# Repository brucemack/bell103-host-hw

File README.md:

Overview
========

Complete Bell 103 subscriber line interface simulator.

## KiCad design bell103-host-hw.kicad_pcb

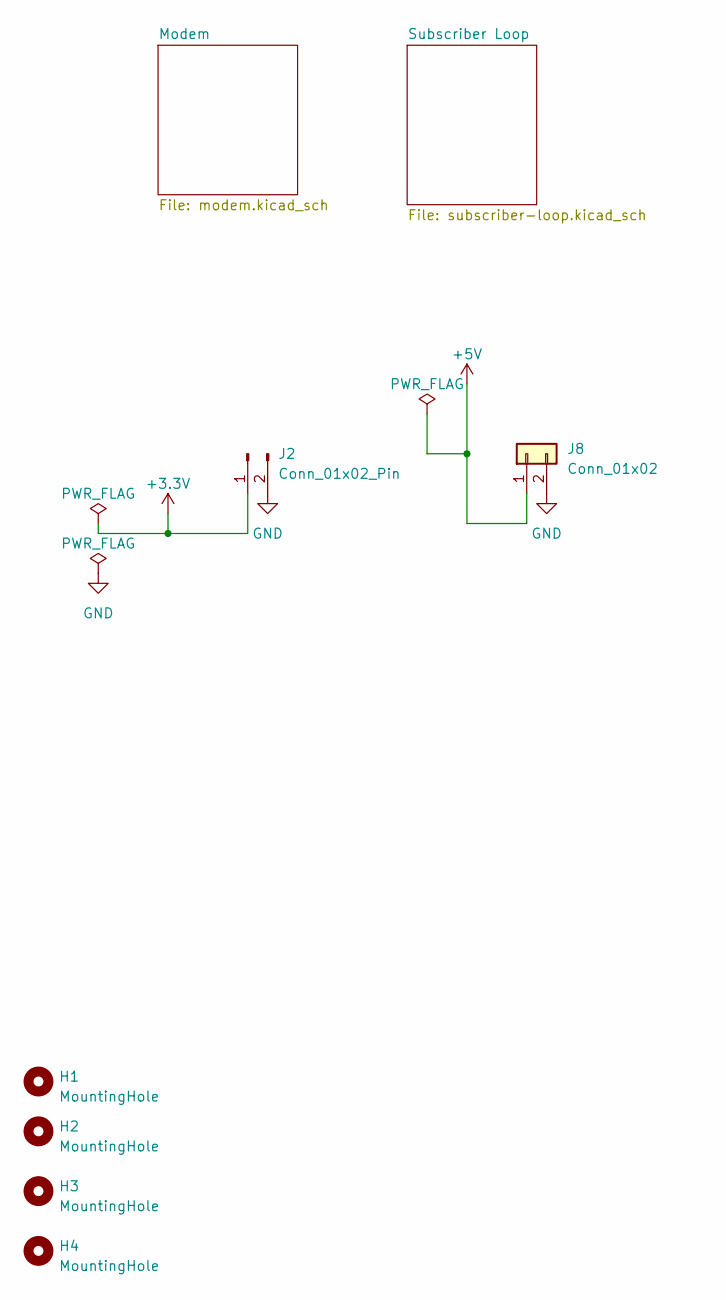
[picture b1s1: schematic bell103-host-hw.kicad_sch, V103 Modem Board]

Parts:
H1, H2, H3, H4: MountingHole; MountingHole_4mm
J2: Conn_01x02_Pin; PinHeader_1x02_P2.54mm_Vertical
J8: Conn_01x02; PinHeader_1x02_P2.54mm_Vertical

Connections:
+3.3V: J2.1; also elsewhere on the board
+5V: J8.1; also elsewhere on the board
GND: J2.2, J8.2; also elsewhere on the board

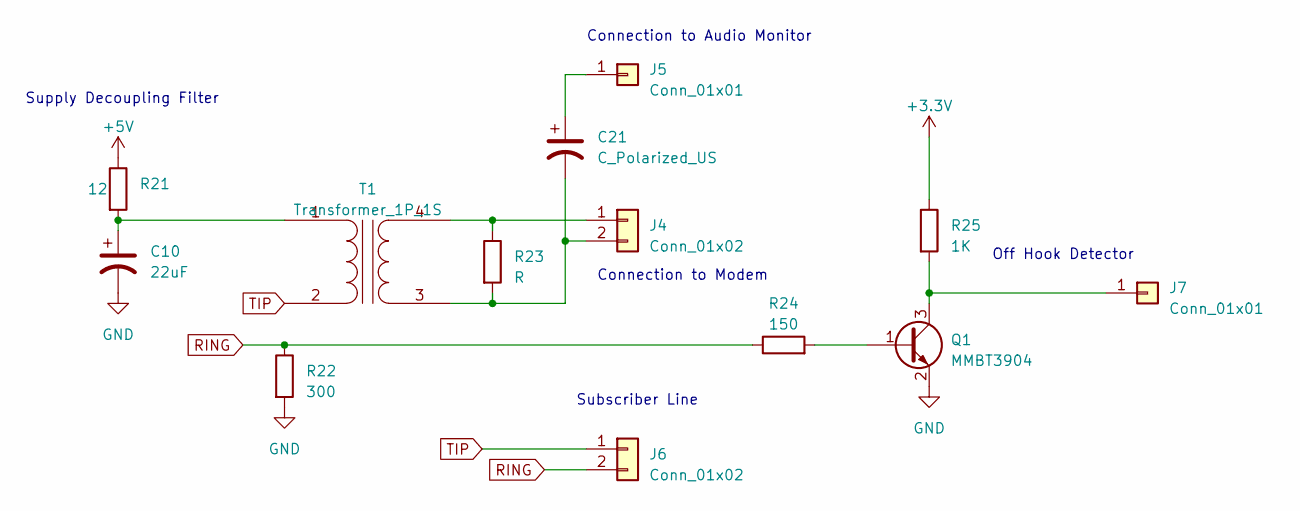
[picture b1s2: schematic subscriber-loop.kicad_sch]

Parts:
C10: 22uF; CP_Radial_D5.0mm_P2.50mm
C21: C_Polarized_US; CP_Radial_D5.0mm_P2.50mm
J4, J6: Conn_01x02; PinHeader_1x02_P2.54mm_Vertical
J5, J7: Conn_01x01; PinHeader_1x01_P2.54mm_Vertical
Q1: MMBT3904; SOT-23
R21: 12; R_0805_2012Metric_Pad1.20x1.40mm_HandSolder
R22: 300; R_0805_2012Metric_Pad1.20x1.40mm_HandSolder
R23: R; R_0805_2012Metric_Pad1.20x1.40mm_HandSolder
R24: 150; R_0805_2012Metric_Pad1.20x1.40mm_HandSolder
R25: 1K; R_0805_2012Metric_Pad1.20x1.40mm_HandSolder
T1: Transformer_1P_1S; Audio_Transformer

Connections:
+3.3V: R25.1; also elsewhere on the board
+5V: R21.1; also elsewhere on the board
GND: C10.2, Q1.2 (E), R22.2; also elsewhere on the board
unnamed: J4.1, R23.1, T1.4 (SB)
unnamed: C21.2, J4.2, R23.2, T1.3 (SA)
unnamed: C21.1, J5.1
unnamed: J7.1, Q1.3 (C), R25.2
unnamed: Q1.1 (B), R24.2
unnamed: C10.1, R21.2, T1.1 (AA)
RING: J6.2, R22.1, R24.1
TIP: J6.1, T1.2 (AB)

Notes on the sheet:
Connection to Audio Monitor
Subscriber Line
Supply Decoupling Filter
Connection to Modem
Off Hook Detector

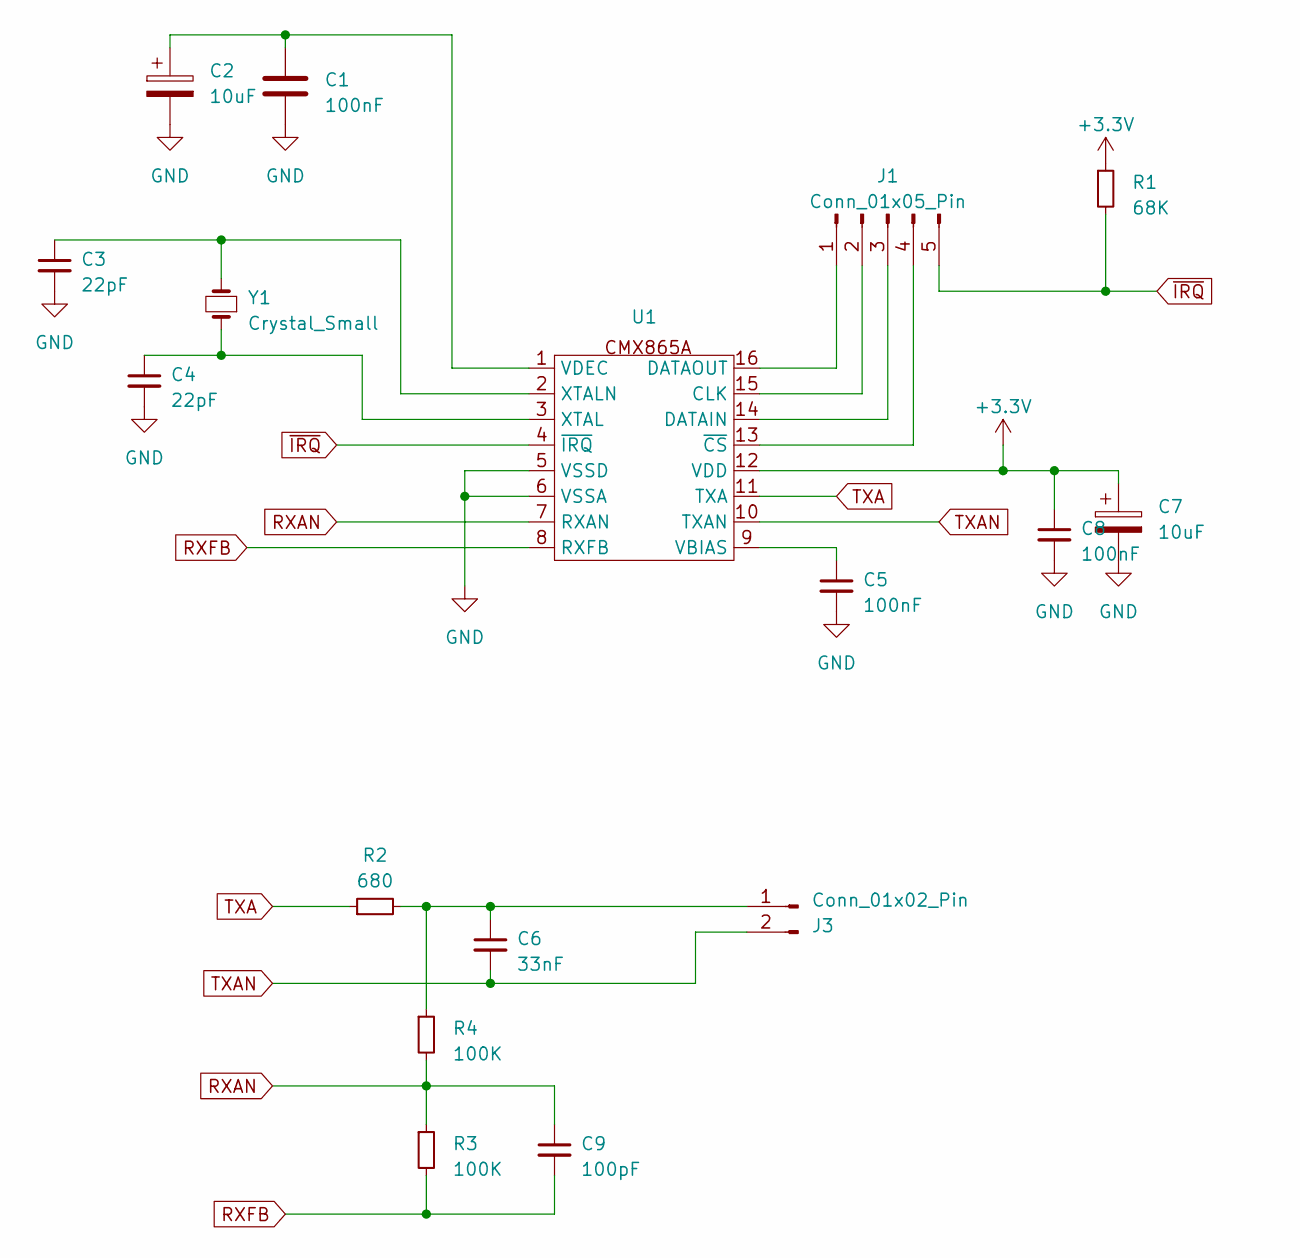
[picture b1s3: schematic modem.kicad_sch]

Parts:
C1, C5, C8: 100nF; C_0805_2012Metric_Pad1.18x1.45mm_HandSolder
C2, C7: 10uF; CP_Radial_D5.0mm_P2.50mm
C3, C4: 22pF; C_0805_2012Metric_Pad1.18x1.45mm_HandSolder
C6: 33nF; C_0805_2012Metric_Pad1.18x1.45mm_HandSolder
C9: 100pF; C_0805_2012Metric_Pad1.18x1.45mm_HandSolder
J1: Conn_01x05_Pin; PinHeader_1x05_P2.54mm_Vertical
J3: Conn_01x02_Pin; PinHeader_1x02_P2.54mm_Vertical
R1: 68K; R_0805_2012Metric_Pad1.20x1.40mm_HandSolder
R2: 680; R_0805_2012Metric_Pad1.20x1.40mm_HandSolder
R3, R4: 100K; R_0805_2012Metric_Pad1.20x1.40mm_HandSolder
U1: SOIC-16W_7.5x12.8mm_P1.27mm
Y1: Crystal_Small; Crystal_HC49-U_Vertical

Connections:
+3.3V: C7.1, C8.1, R1.1, U1.12 (VDD); also elsewhere on the board
GND: C1.2, C2.2, C3.2, C4.2, C5.2, C7.2, C8.2, U1.5 (VSSD), U1.6 (VSSA); also elsewhere on the board
unnamed: J1.1, U1.16 (DATAOUT)
unnamed: J1.2, U1.15 (CLK)
unnamed: J1.3, U1.14 (DATAIN)
unnamed: J1.4, U1.13 (~CS)
unnamed: C6.1, J3.1, R2.2, R4.1
unnamed: C5.1, U1.9 (VBIAS)
unnamed: C1.1, C2.1, U1.1 (VDEC)
unnamed: C4.1, U1.3 (XTAL), Y1.1
unnamed: C3.1, U1.2 (XTALN), Y1.2
RXAN: C9.1, R3.1, R4.2, U1.7 (RXAN)
RXFB: C9.2, R3.2, U1.8 (RXFB)
TXA: R2.1, U1.11 (TXA)
TXAN: C6.2, J3.2, U1.10 (TXAN)
~IRQ: J1.5, R1.2, U1.4 (~IRQ)

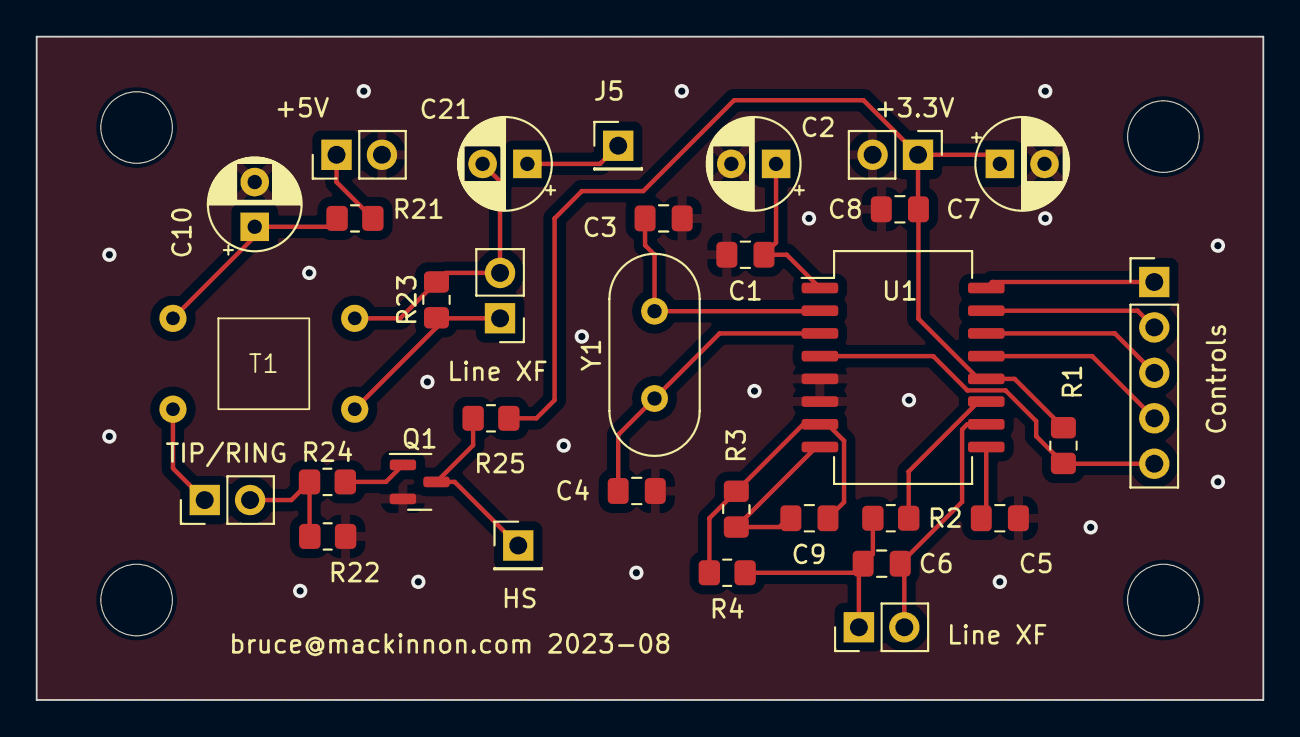
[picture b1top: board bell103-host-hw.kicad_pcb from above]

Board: 2 copper layers, 68.6 x 37.1 mm, 36 parts (0 on the bottom side), 25 nets.

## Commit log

2023-08-20 Added a few more vias
2023-08-20 Added docs
2023-08-20 Improved docs
